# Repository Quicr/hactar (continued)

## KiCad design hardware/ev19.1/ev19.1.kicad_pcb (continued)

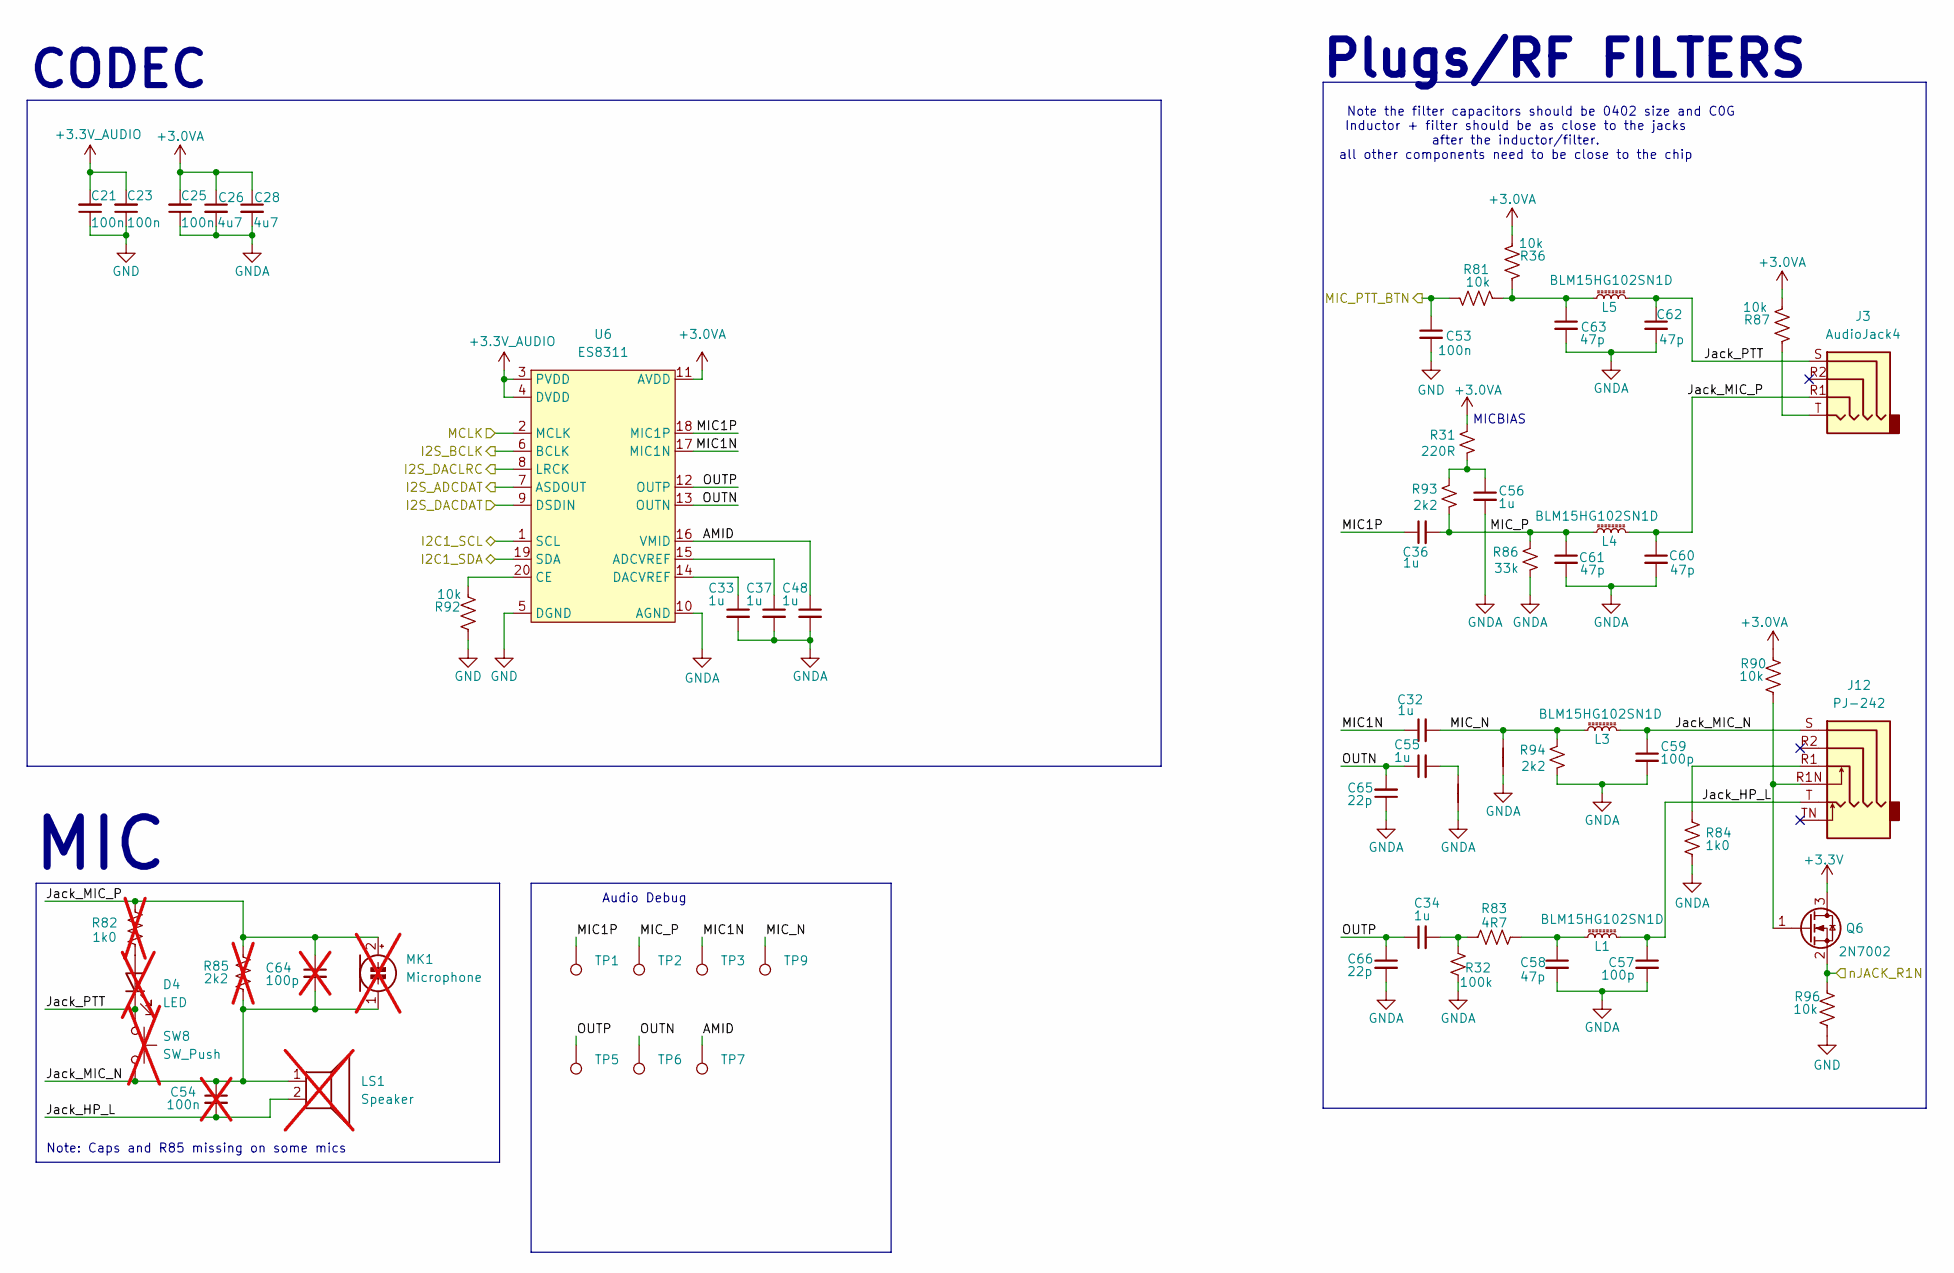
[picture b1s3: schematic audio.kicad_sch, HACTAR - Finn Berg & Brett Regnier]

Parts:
C21, C23, C25, C53: 100n; C_0402_1005Metric; JLCPCB Part # C1525
C26, C28: 4u7; C_0402_1005Metric; JLCPCB Part # C23733
C32, C33, C36, C37, C48, C56: 1u; C_0402_1005Metric; JLCPCB Part # C52923
C34, C55: 1u; C_0603_1608Metric; JLCPCB Part # C15849
C54: 100n; not fitted
C57, C59: 100p; C_0402_1005Metric; JLCPCB Part # C1546
C58, C60, C61, C62, C63: 47p; C_0402_1005Metric; JLCPCB Part # C1567
C64: 100p; not fitted
C65, C66: 22p; C_0603_1608Metric; JLCPCB Part # C1653
D4: LED; not fitted
J3: AudioJack4; AUDIO-SMD_PJ-320D; JLCPCB Part # C431535
J12: PJ-242; AUDIO-SMD_PJ-242D-SMT; JLCPCB Part # C431536
L1, L3, L4, L5: BLM15HG102SN1D; L_0402_1005Metric; JLCPCB Part # C76889
LS1: Speaker; not fitted
MK1: Microphone; not fitted
NT11, NT12: NetTie_2; NetTie-2_SMD_Pad0.5mm
Q6: 2N7002; SOT-23; JLCPCB Part # C8545
R31: 220R; R_0603_1608Metric; JLCPCB Part # C22962
R32: 100k; R_0402_1005Metric; JLCPCB Part # C25741
R36, R81, R87, R90, R92, R96: 10k; R_0402_1005Metric; JLCPCB Part # C25744
R82: 1k0; not fitted
R83: 4R7; R_0603_1608Metric; JLCPCB Part # C23164
R84: 1k0; R_0402_1005Metric; JLCPCB Part # C11702
R85: 2k2; not fitted
R86: 33k; R_0402_1005Metric; JLCPCB Part # C25779
R93, R94: 2k2; R_0603_1608Metric; JLCPCB Part # C4190
SW8: SW_Push; not fitted
TP1, TP2, TP3, TP5, TP6, TP7, TP9: TestPoint; TestPoint_THTPad_D2.0mm_Drill1.0mm
U6: ES8311; JLCPCB Part # C962342

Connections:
+3.0VA: C25.2, C26.1, C28.1, R31.2, R36.2, R87.2, R90.1, U6.11 (AVDD); also elsewhere on the board
+3.3V: Q6.3 (D); also elsewhere on the board
+3.3V_AUDIO: C21.2, C23.2, U6.3 (PVDD), U6.4 (DVDD); also elsewhere on the board
/Audio/AMID: C48.1, TP7.1 (1_1), U6.16 (VMID)
/Audio/Jack_HP_L: C54.2, C57.1, J12.T, L1.2, LS1.2
/Audio/Jack_MIC_N: C54.1, C59.1, C64.2, J12.S, L3.2, LS1.1, MK1.1 (-), R85.2, SW8.2
/Audio/Jack_MIC_P: C60.1, C64.1, J3.R1, L4.1, MK1.2 (+), R82.1, R85.1
/Audio/Jack_PTT: C62.1, D4.1 (K), J3.S, L5.1, SW8.1
/Audio/MIC1N: C32.1, TP3.1 (1_1), U6.17 (MIC1N)
/Audio/MIC1P: C36.1, TP1.1 (1_1), U6.18 (MIC1P)
/Audio/MIC_N: C32.2, L3.1, NT12.2, R94.2, TP9.1 (1_1)
/Audio/MIC_P: C36.2, C61.1, L4.2, R86.2, R93.1, TP2.1 (1_1)
/Audio/MIC_PTT_BTN: C53.1, R81.2; also elsewhere on the board
/Audio/OUTN: C55.1, C65.2, TP6.1 (1_1), U6.13 (OUTN)
/Audio/OUTP: C34.1, C66.1, TP5.1 (1_1), U6.12 (OUTP)
/Audio/nJACK_R1N: Q6.2 (S), R96.1; also elsewhere on the board
/I2C1_SCL: U6.1 (SCL); also elsewhere on the board
/I2C1_SDA: U6.19 (SDA); also elsewhere on the board
/I2S_ADCDAT: U6.7 (ASDOUT); also elsewhere on the board
/I2S_BCLK: U6.6 (BCLK); also elsewhere on the board
/I2S_DACDAT: U6.9 (DSDIN); also elsewhere on the board
/I2S_DACLRC: U6.8 (LRCK); also elsewhere on the board
/MCLK: U6.2 (MCLK); also elsewhere on the board
GND: C21.1, C23.1, C53.2, R92.1, R96.2, U6.5 (DGND); also elsewhere on the board
GNDA: C25.1, C26.2, C28.2, C33.2, C37.2, C48.2, C56.2, C57.2, C58.2, C59.2, C60.2, C61.2, C62.2, C63.2, C65.1, C66.2, NT11.1, NT12.1, R32.1, R84.2, R86.1, R94.1, U6.10 (AGND), U6.21 (PAD); also elsewhere on the board
unnamed: C34.2, R32.2, R83.1
unnamed: C55.2, NT11.2
unnamed: C56.1, R31.1, R93.2
unnamed: C58.1, L1.1, R83.2
unnamed: C63.1, L5.2, R36.1, R81.1
unnamed: D4.2 (A), R82.2
unnamed: J3.T, R87.1
unnamed: J12.R1, R84.1
unnamed: J12.R1N, Q6.1 (G), R90.2
unnamed: C37.1, U6.15 (ADCVREF)
unnamed: R92.2, U6.20 (CE)
unnamed: C33.1, U6.14 (DACVREF)

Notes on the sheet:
Inductor + filter should be as close to the jacks after the inductor/filter. all other components need to be close to the chip
Audio Debug
CODEC
Note: Caps and R85 missing on some mics
MIC
Plugs/RF FILTERS
Note the filter capacitors should be 0402 size and C0G
MICBIAS

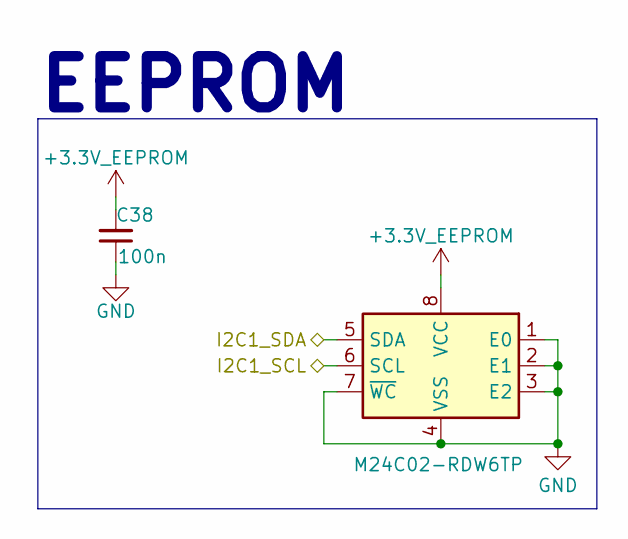
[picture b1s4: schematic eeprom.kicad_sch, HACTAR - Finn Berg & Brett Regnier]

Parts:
C38: 100n; C_0402_1005Metric; JLCPCB Part # C1525
U8: M24C02-RDW6TP; TSSOP-8_4.4x3mm_P0.65mm; JLCPCB Part # C152731

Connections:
+3.3V_EEPROM: C38.2, U8.8 (VCC); also elsewhere on the board
/I2C1_SCL: U8.6 (SCL); also elsewhere on the board
/I2C1_SDA: U8.5 (SDA); also elsewhere on the board
GND: C38.1, U8.1 (E0), U8.2 (E1), U8.3 (E2), U8.4 (VSS), U8.7 (~WC); also elsewhere on the board

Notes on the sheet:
EEPROM

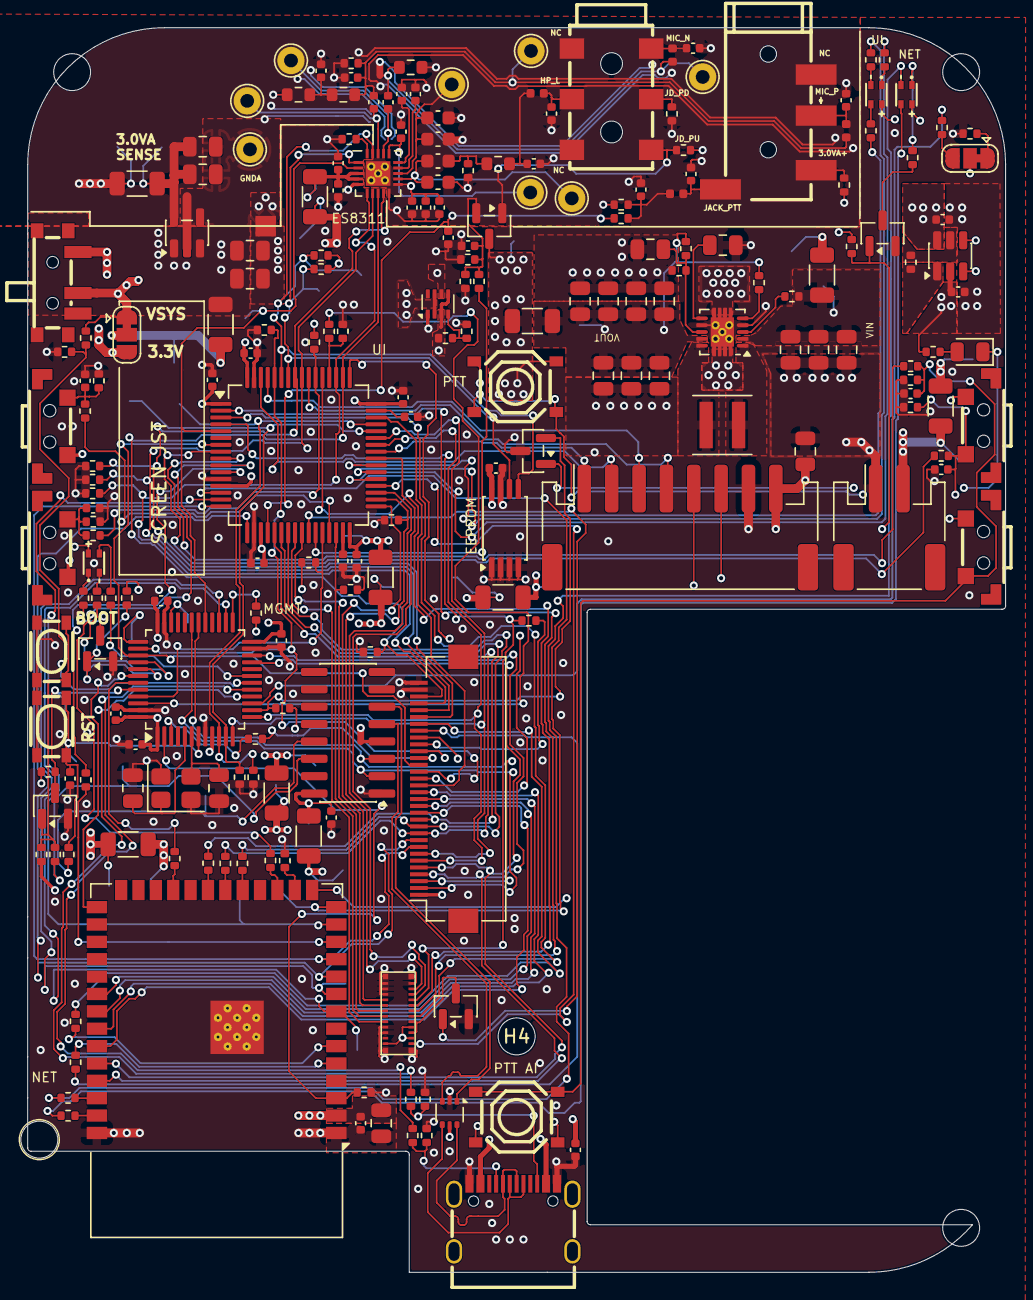
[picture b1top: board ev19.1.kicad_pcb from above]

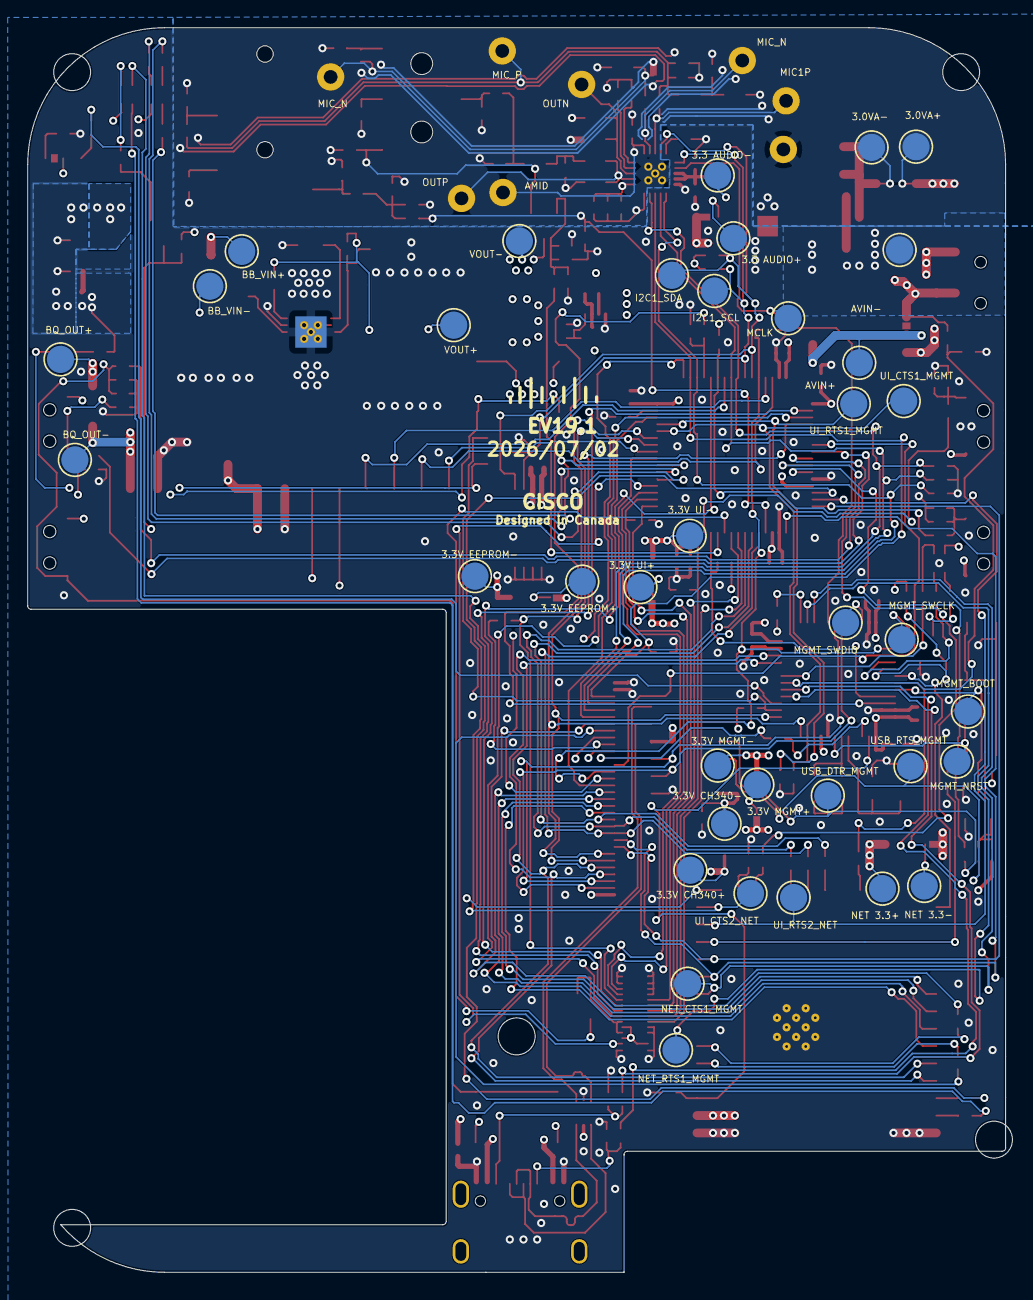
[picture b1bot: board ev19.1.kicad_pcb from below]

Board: 4 copper layers, 71.5 x 91.0 mm, 265 parts (37 on the bottom side), 190 nets.

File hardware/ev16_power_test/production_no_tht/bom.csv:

Designator,Footprint,Quantity,Value,LCSC Part #
"C1, C13, C17, C21, C23, C25, C38, C39, C40, C41, C42, C43, C46, C47, C49, C50, C6, C8, C9",0402,19,100n,C1525
"C10, C11, C14, C19, C22",0805,5,100n,C85866
"C12, C4, C5",0402,3,10u,C307415
"C15, C16",0805,2,10u,C17024
"C18, C32, C36, C7",0402,4,1u,C52923
"C2, C3",0805,2,33p,C107115
C20,0805,1,2p2,C519933
"C24, C27, C29, C30, C31, C35",0805,6,22u,C5674
"C26, C28, C33, C37",0402,4,4u7,C23733
"C34, C48",1206,2,100u,C15008
"C44, C45",0402,2,2u2,C12530
CN1,IDC-SMD_10P-P1.27_X1270WVS-2X05B-6TV01,1,Conn_05x02_Female,C2962222
CN2,AUDIO-SMD_PJ-242D-SMT,1,PJ-242,C431536
D1,0805,1,LED,C130114
D5,LED-ARRAY-SMD_4P-L1.6-W1.5-TL_NH-B1515RGBA,1,LED_BGAR,C2874115
"D7, D9",LED-ARRAY-SMD_HS-1204-RGB,2,LED_BGAR,C965884
J1,USB-C_SMD-TYPE-C-31-M-12,1,USB_C_Receptacle,C165948
"J11, J6, J7, J8, J9",HDR-SMD_10P-P2.54-V-F-R2-C5-LS7.1-1,5,Conn_02x05_Counter_Clockwise,C3975150
J2,JST_PH_S2B-PH-SM4-TB_1x02-1MP_P2.00mm_Horizontal,1,Conn_01x02_Socket,C295747
J3,AUDIO-SMD_PJ-320D,1,AudioJack4,C431535
"J4, J5",HDR-SMD_6P-P2.54-V-M-R2-C3-LS7.5-2,2,Conn_02x03_Odd_Even, C3294461
L2,L_Coilcraft_XxL4020,1,1.5uH,C3033018
"Q1, Q2, Q3",SOT-23,3,2N7002,C8545
R1,0402,1,680R,C25130
"R10, R17, R24, R4, R40, R44, R45, R46, R49, R5, R50, R57, R58, R70, R71, R72, R73, R74, R9",0402,19,1k0,C11702
"R11, R16, R19",0402,3,1k5,C25867
"R12, R47, R6",0402,3,10k,C25744
"R13, R29, R53",0402,3,15k,C25756
"R14, R48, R52",0603,3,0R1,C111027
"R15, R33, R56",0402,3,180R,C25087
"R18, R28, R32, R65, R75",0402,5,100k,C25741
"R2, R22, R23, R30, R36, R37, R38, R39, R41, R42, R43, R51, R54, R55, R61, R62, R66, R67, R68, R69",0402,20,4k7,C25900
"R20, R21, R34, R35, R59, R60",0402,6,150R,C25082
"R25, R3, R64",0402,3,47k,C25792
R26,0402,1,360k, C45956
R27,0402,1,64k9,C26984
R31,0402,1,2k2,C25879
"R7, R8",0402,2,5k1,C25905
"SW2, SW3",KEY-SMD_4P-L4.2-W3.2-P2.20-LS4.6,2,SW_Push,C139797
"SW4, SW5",SW-SMD_4P-L5.1-W5.1-P3.70-LS6.5-TL_H1.5,2,SW_Push,C318884
"SW6, SW7",SW-SMD_SHOU_TS36CA-0.6,2,SW_Push,C2906288
U1,SOT-23-6,1,BQ21040DBV,C202311
U10,LQFP-64_10x10mm_P0.5mm,1,STM32F405RGTx,C15742
U12,SOT-23-5,1,XC6227C301MR-G,C484285
U2,SOT-666,1,USBLC6-2P6,C2827693
U3,LQFP-48_7x7mm_P0.5mm,1,STM32F072CBTx,C80488
U4,SOIC-16_3.9x9.9mm_P1.27mm,1,CH340C,C84681
U5,Texas_S-PWSON-N10_ThermalVias,1,TPS63060,C48567
U6,QFN-32-1EP_5x5mm_P0.5mm_EP3.45x3.45mm_ThermalVias,1,WM8960CGEFL/RV,C18752
U7,ESP32-S3-WROOM-1,1,ESP32-S3-WROOM-1,C2913204
U8,SOIC-8_3.9x4.9mm_P1.27mm,1,M24C02-RMN6TP,C83836
U9,SOT-583-8,1,TPS2116DRL,C3235557
Y1,Crystal_SMD_3225-4Pin_3.2x2.5mm,1,Crystal_GND24,C13738

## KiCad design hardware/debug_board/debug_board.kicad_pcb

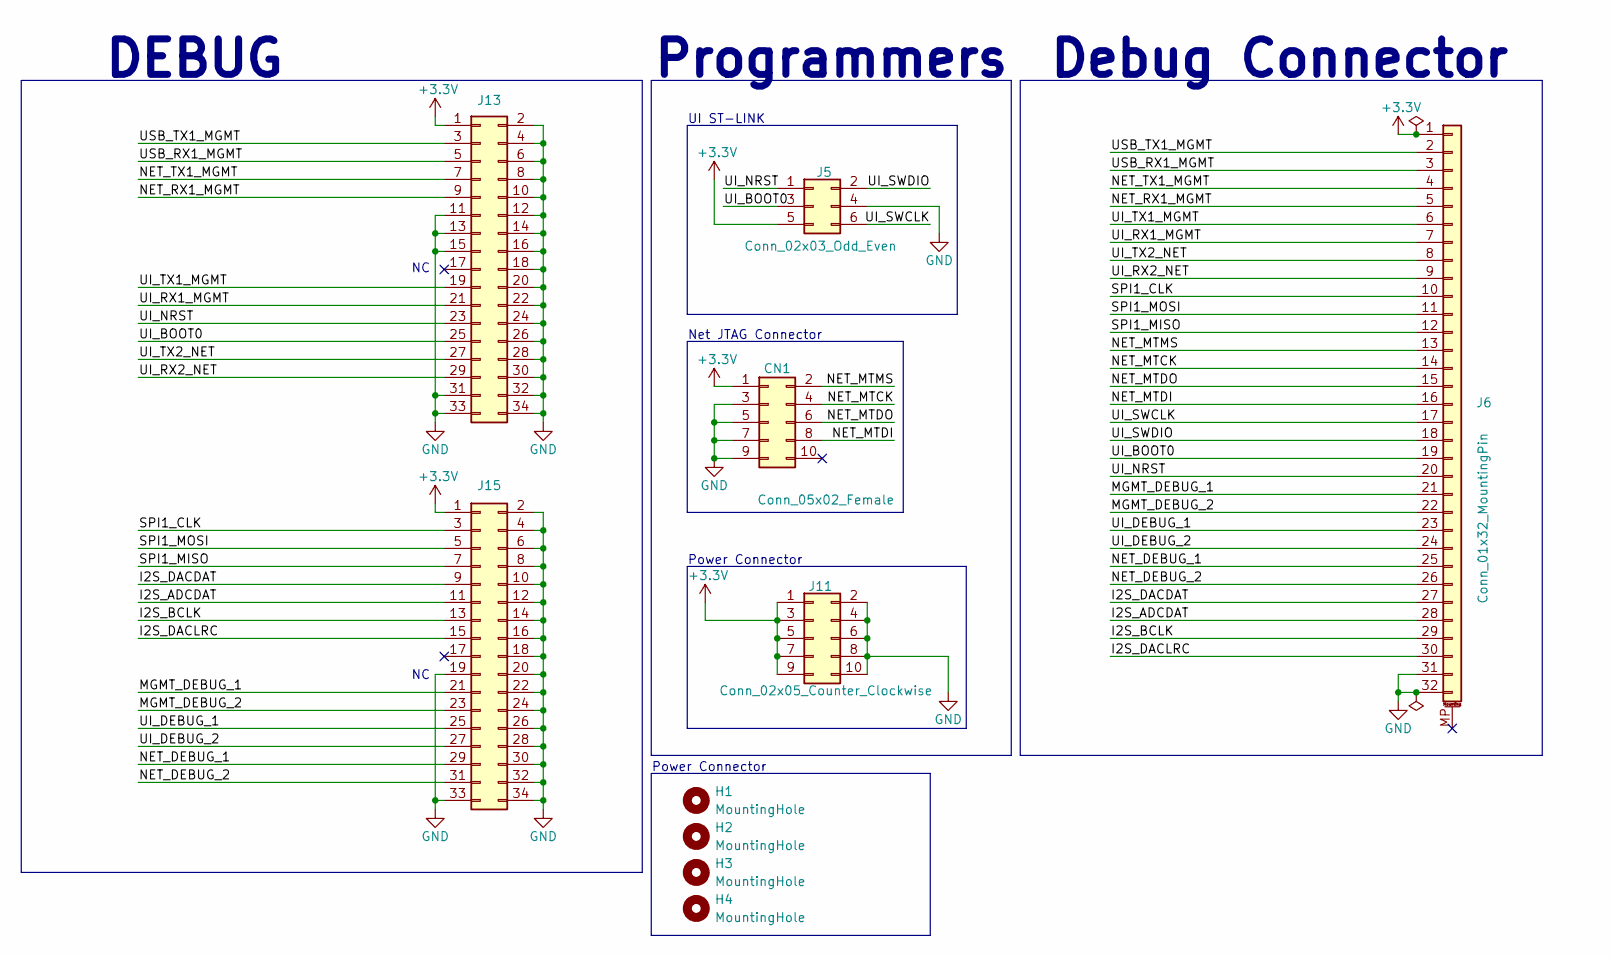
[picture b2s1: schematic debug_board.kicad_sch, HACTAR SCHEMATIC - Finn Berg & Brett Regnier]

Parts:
CN1: Conn_05x02_Female; IDC-SMD_10P-P1.27_X1270WVS-2X05B-6TV01; JLCPCB Part # C2962222
H1, H2, H3, H4: MountingHole; MountingHole_2.7mm_M2.5
J5: Conn_02x03_Odd_Even; PinHeader_2x03_P2.54mm_Vertical_SMD; JLCPCB Part # C3294461
J6: Conn_01x32_MountingPin; Hirose_FH12-32S-0.5SH_1x32-1MP_P0.50mm_Horizontal; JLCPCB Part # C597985
J11: Conn_02x05_Counter_Clockwise; PinSocket_2x05_P2.54mm_Vertical_SMD; JLCPCB Part # C3975150
J13, J15: Conn_02x17_Counter_Clockwise; PinHeader_2x17_P2.54mm_Vertical_SMD; JLCPCB Part # C22436164

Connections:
+3.3V: CN1.1, J5.5, J6.1, J11.1, J11.3, J11.5, J11.7, J11.9, J13.1, J15.1
/I2S_ADCDAT: J6.28, J15.11
/I2S_BCLK: J6.29, J15.13
/I2S_DACDAT: J6.27, J15.9
/I2S_DACLRC: J6.30, J15.15
/MGMT_DEBUG_1: J6.21, J15.21
/MGMT_DEBUG_2: J6.22, J15.23
/NET_DEBUG_1: J6.25, J15.29
/NET_DEBUG_2: J6.26, J15.31
/NET_MTCK: CN1.4, J6.14
/NET_MTDI: CN1.8, J6.16
/NET_MTDO: CN1.6, J6.15
/NET_MTMS: CN1.2, J6.13
/NET_RX1_MGMT: J6.5, J13.9
/NET_TX1_MGMT: J6.4, J13.7
/SPI1_CLK: J6.10, J15.3
/SPI1_MISO: J6.12, J15.7
/SPI1_MOSI: J6.11, J15.5
/UI_BOOT0: J5.3, J6.19, J13.25
/UI_DEBUG_1: J6.23, J15.25
/UI_DEBUG_2: J6.24, J15.27
/UI_NRST: J5.1, J6.20, J13.23
/UI_RX1_MGMT: J6.7, J13.21
/UI_RX2_NET: J6.9, J13.29
/UI_SWCLK: J5.6, J6.17
/UI_SWDIO: J5.2, J6.18
/UI_TX1_MGMT: J6.6, J13.19
/UI_TX2_NET: J6.8, J13.27
/USB_RX1_MGMT: J6.3, J13.5
/USB_TX1_MGMT: J6.2, J13.3
GND: CN1.3, CN1.5, CN1.7, CN1.9, J5.4, J6.31, J6.32, J11.2, J11.4, J11.6, J11.8, J11.10, J13.2, J13.4, J13.6, J13.8, J13.10, J13.11, J13.12, J13.13, J13.14, J13.15, J13.16, J13.18, J13.20, J13.22, J13.24, J13.26, J13.28, J13.30, J13.31, J13.32, J13.33, J13.34, J15.2, J15.4, J15.6, J15.8, J15.10, J15.12, J15.14, J15.16, J15.18, J15.19, J15.20, J15.22, J15.24, J15.26, J15.28, J15.30, J15.32, J15.33, J15.34

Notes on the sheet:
Programmers
UI ST-LINK
Net JTAG Connector
DEBUG
Power Connector
Debug Connector

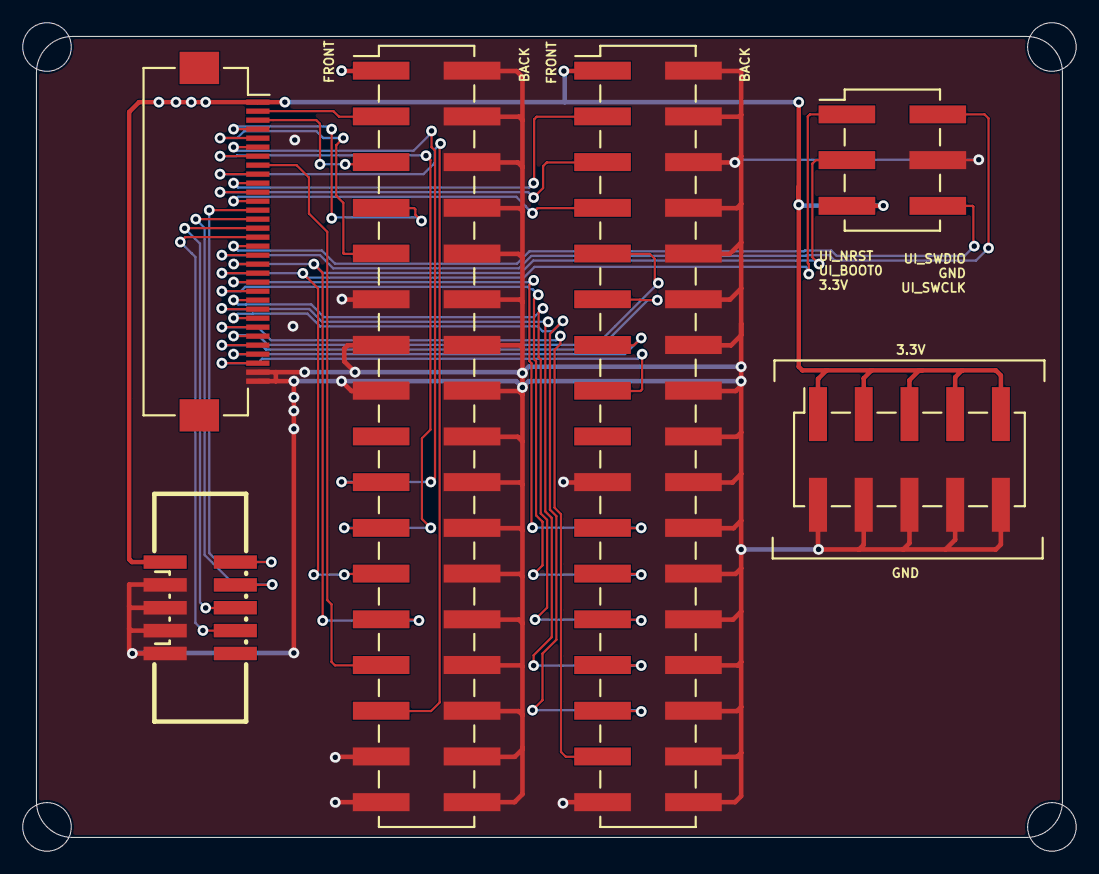
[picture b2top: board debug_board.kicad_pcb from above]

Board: 4 copper layers, 57.0 x 44.5 mm, 10 parts (0 on the bottom side), 31 nets.
